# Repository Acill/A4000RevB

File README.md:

# A4000 Replica Project (Based on the Rev B)
Amiga 4000 Replica project. Based on the A4000 Rev B and organized by Paul Rezendes and the generous contributions of the Amiga Community. 

*** IF YOU WISH TO PRODUCE YOUR OWN BOARDS PLEASE USE THE NEW GERBERS LOCATED HERE: https://github.com/Acill/A4000RevB/tree/master/Gerbers-JLCPCB ***

ASCII (PADS) export has been added are are located into the ASCII folder. You can use this to import into other EDA applications. 

By popular request I have added the project into Kicad. its available in the Kicad folder. Please commit any change back here and document them. 

IF YOU PRODUCE BOARDS USING ORIGINAL PROJECT FILES YOU ***MUST*** TELL THE FACTORY TO IMPORT THE GERBERS AS A ***MENTOR PADS FORMAT PROJECT*** The gerbers located here are already good for use as JLCPCB. please read firther information in the gerber section. 

***Thank you Chucky for the locator build hosting! I recomend all go here during your builds for some great help!
A4000 Locator Site: http://locator.reamiga.info/locator.php?project=A4000***

***A4000 Build Guide, Thanks to Chucky! https://wordpress.hertell.nu/?p=1053***

***Shred made a great repo for an updated BOM. Thank you! Please visit the new BOM here: https://a4000-bom.shred.codefloe.page/***

READ THIS: New board files and gerbers have been created and posted to the Github project page. A minor error was discovered that had solder mask covering the ground pads for the support bracket on the mouse and joystick ports. Previous boards work just fine and are not in danger of not working. This is more of a cosmetic update than anything else. Get the new file in the Gerber folder. When using the Chinese sites like JLPCB and PCBway you will need to upload the complete zip gerber archive and email them about the board design. It is done in Mentor PADs. This is a professional layout and it will not usually work with the automatic software they use. I have produced these here in the US and have no problems. Others have used JLPCB with no problems as well. I f you would like a single board and need help I can order sets of 5 and would be happy to sell you one. You can email me through the contact page or directly at info@acill.com and request one. Currently they run $95 shipped in the USA and $110 international.  

# Images

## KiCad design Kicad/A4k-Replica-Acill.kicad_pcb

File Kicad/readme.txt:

Its been a long over due wait, but here is the project in Kicad at last. Please continue to merge here and comment any updates. 

Project and schematics are together in the 7zip archive.

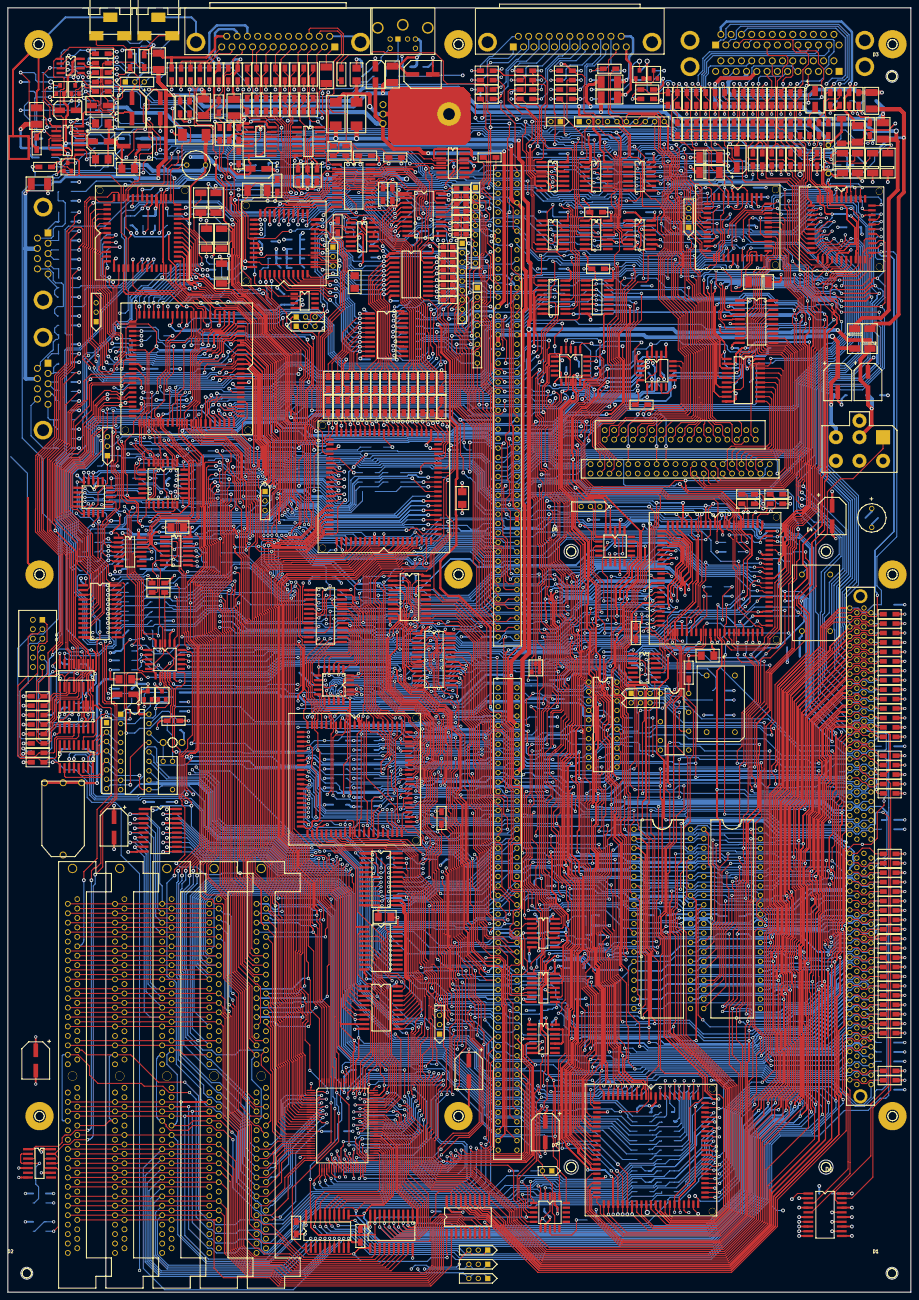
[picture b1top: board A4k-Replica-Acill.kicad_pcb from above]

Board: 4 copper layers, 243.1 x 345.7 mm, 791 parts (0 on the bottom side), 882 nets.

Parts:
BT176: PACKAGE_0000
C102: PACKAGE_0001
C103, C106, C130, C131, C140, C141, C145, C152, C154A, C154B, C193, C195, C201, C211B, C211C, C212, C213, C215, C216, C305, C311, C352, C353, C354, C355, C402A, C406H, C411, C412, C413, C430, C432, C441, C447, C455, C455B, C456, C456B, C457, C457B, C459, C460A, C460B, C460E, C460F, C485, C860, C892: PACKAGE_0002
C104, C177, C178, C179, C205, C211A, C250A, C250C, C300, C350, C400B, C402B, C409, C414, C446, C458B, C460C, C460D, C500, C890, C891, C901, C902, C903, C904, C975, C976, C990: PACKAGE_0003
C150, C406, C708, C711: PACKAGE_0004
C175, C176, C703, C704, C706, C707, C710: PACKAGE_0005
C181, C407: PACKAGE_0006
C185: PACKAGE_0007
C186: PACKAGE_0008
C187, C188, C189, C190, C191, C192, C194, C196, C408: PACKAGE_0009
C198, C318: PACKAGE_0010
C199: PACKAGE_0011
C200, C433, C460G: PACKAGE_0012
C317: PACKAGE_0013
C351, C431: PACKAGE_0014
C400A: PACKAGE_0015
C403, C405, C701: PACKAGE_0016
C404, C443: PACKAGE_0017
C440, C907: PACKAGE_0018
C442, C511, C512, C513, C893, C894: PACKAGE_0019
C450: PACKAGE_0020
C458: PACKAGE_0021
C700, C702, C714: PACKAGE_0022
CN160: PACKAGE_0023
CN175: PACKAGE_0024
CN200, CN302, CN303: PACKAGE_0025
CN300: PACKAGE_0026
CN350: PACKAGE_0027
CN351: PACKAGE_0028
CN352: PACKAGE_0029
CN402, CN403: PACKAGE_0030
CN404: PACKAGE_0031
CN450: PACKAGE_0032
CN452, CN600: PACKAGE_0033
CN651: PACKAGE_0034
CN900: PACKAGE_0035
CN975, CN976: PACKAGE_0036
D1, D2, D3: MTHOLE125-NPT; MTH-125-NPT
D4, D5, D6, D7: MTHOLE150-NPT; MTH-150-NPT
D175: PACKAGE_0037
D176, D360, D361, D362, D363, D500, D501, D502, D503, D504, D505: PACKAGE_0038
D177: PACKAGE_0039
D178: PACKAGE_0040
D300: PACKAGE_0041
D305: PACKAGE_0042
D306, D307: PACKAGE_0043
D507: PACKAGE_0044
EC182, EC184, EC410, EC411: PACKAGE_0003
EC183, EC309, EC362, EC363, EC365, EC366, EC379, EC976, EC977, EC978, EC979, EC980, EC981, EC982, EC983, EC984, EC985, EC986, EC987, EC988, EC989: PACKAGE_0002
EC300, EC301, EC302, EC305, EC306, EC308, EC350, EC351, EC352, EC353, EC354, EC355, EC356, EC357, EC358, EC359, EC360, EC361, EC364: PACKAGE_0019
EC303, EC304, EC451, EC452, EC453, EC454, EC455, EC456, EC457, EC458, EC459, EC460, EC461, EC462, EC463, EC464: PACKAGE_0001
EC307: PACKAGE_0045
EC367, EC371, EC372, EC375, EC376, EC378: PACKAGE_0018
EC368, EC369, EC370, EC373, EC374, EC377: PACKAGE_0014
ER175, ER176: PACKAGE_0003
ER300, ER301, ER302, ER303, ER304, ER305, ER306, ER307, ER363, ER453, ER458, ER459, ER460, ER461: PACKAGE_0001
ER350, ER351, ER352, ER353, ER354, ER355, ER356, ER357, ER358, ER359, ER360, ER361, ER475: PACKAGE_0019
ER362, ER976, ER977, ER978, ER979, ER980, ER981, ER982, ER983, ER984, ER985, ER986, ER987, ER988, ER989: PACKAGE_0002
ER367, ER369, ER370, ER373, ER374, ER377, ER379: PACKAGE_0045
ER368, ER371, ER372, ER375, ER376, ER378: PACKAGE_0021
F175: PACKAGE_0046
FB177, FB308, FB309, FB463, FB476: PACKAGE_0047
FB364, FB401, FB462, FB464: PACKAGE_0048
FB365, FB366, FB975: PACKAGE_0049
FB410, FB411: PACKAGE_0019
FB710: PACKAGE_0001
J100: PACKAGE_0052
J104, J501, J502: PACKAGE_0031
J151: PACKAGE_0053
J212, J214, J852: PACKAGE_0054
J213, J500: PACKAGE_0055
J351, J850: PACKAGE_0056
J352: PACKAGE_0057
J975: PACKAGE_0058
L500: PACKAGE_0011
MT1, MT2, MT3, MT4, MT5, MT6, MT7, MT8, MT9: PACKAGE_0065
Q300, Q901: PACKAGE_0041
Q400: PACKAGE_0039
Q430: PACKAGE_0068
Q440: PACKAGE_0040
R1, R9, R10, R11, R12, R13, R14, R17, R18, R19, R20, R21, R22, R23, R32, R41, R42, R43, R44, R45, R46, R47, R48, R49, R50, R51, R52, R53, R54, R55, R56, R66, R67, R70, R74, R77, R78, R81, R82, R83, R85, R239, R432, R443, R513, R546, R702, R902, R912, R981, R982, R983, R984, R985, R989, R993, R994: PACKAGE_0021
R2, R3, R4, R5, R6, R7, R8, R15, R16, R24, R25, R26, R27, R28, R29, R30, R31, R33, R34, R35, R36, R37, R38, R39, R40, R57, R58, R59, R60, R61, R62, R63, R64, R65, R68, R71, R72, R73, R75, R76, R79, R80, R84, R86, R87, R88, R101, R102, R104, R111, R120, R126, R151, R162, R166, R171, R172, R175, R178, R181, R211, R212, R213, R214, R223, R231, R232, R233, R234, R235, R236, R237, R241, R242, R244, R245, R246, R247, R248, R249, R301, R311, R359, R361, R371, R401, R402, R403, R403B, R403F, R407, R408, R430, R433, R440, R442, R445, R451, R465, R502, R504, R508, R510, R511, R548, R614, R615, R616, R618, R619, R620, R621, R622, R630, R632, R633, R634, R652, R660, R661, R701, R704, R709, R710, R711, R712, R721, R722, R861, R904: PACKAGE_0002
R103, R105, R106, R112, R121, R122, R125, R128, R161, R165, R173, R215, R216, R217, R218, R222, R307, R355, R357, R358, R360, R382, R404, R405, R406, R431, R435, R441, R457, R500, R501, R503, R506, R509, R612, R613, R617, R623, R624, R625, R626, R631, R635, R639, R651, R703, R708, R862, R871, R881, R882, R883, R884, R885, R886, R887, R888, R889, R890, R891, R892, R893, R894, R895, R896, R897, R898, R899, R903, R905, R911: PACKAGE_0003
R127, R206, R302, R356, R456, R458, R458A, R458B, R459, R460, R461, R462, R463, R464, R505, R512, R514, R515: PACKAGE_0019
R167, R168, R169, R170, R306, R381, R403A, R403G, R403H, R434, R507, R545, R720: PACKAGE_0045
R176, R177: PACKAGE_0069
R179: PACKAGE_0070
R180, R182, R240, R243, R305, R403C, R403E, R986, R987, R988, R990, R991, R992: PACKAGE_0014
R207, R208, R520, R521, R522, R523, R524, R525, R526, R527, R528, R529, R530, R531, R532, R533, R534, R535, R536, R537, R538, R539, R540, R541, R542, R543, R547: PACKAGE_0001
R383: PACKAGE_0071
R400: PACKAGE_0072
R403D, R444, R975: PACKAGE_0018
R455A, R455B, R455C, R455D, R455E, R455F, R455G, R455H: PACKAGE_0073
R456A, R456B, R456C, R456D, R456E, R456F, R456G, R456H, R457A, R457B, R457C, R457D, R457E, R457F, R457G: PACKAGE_0074
R457H: PACKAGE_0075
RP176: PACKAGE_0076
RP351: PACKAGE_0077
RP461, RP462, RP463: PACKAGE_0078
U102: PACKAGE_0079
U103: PACKAGE_0080
U104, U154: PACKAGE_0081
U106: PACKAGE_0082
U130: PACKAGE_0083
U131: PACKAGE_0084
U140, U351, U352, U355, U402: PACKAGE_0085
U141: PACKAGE_0086
U145, U455, U456, U458, U704, U707, U708, U891, U903, U904: PACKAGE_0087
U150, U700, U890: PACKAGE_0088
U152: PACKAGE_0089
U175: PACKAGE_0090
U176: PACKAGE_0091
U177, U975, U976: PACKAGE_0092
U178: PACKAGE_0093
U198: PACKAGE_0094
U205, U710: PACKAGE_0095
U211: PACKAGE_0096
U212: PACKAGE_0097
U213: PACKAGE_0098
U215, U311: PACKAGE_0099
U216, U702, U703, U706: PACKAGE_0100
U250: PACKAGE_0101
U261, U850, U851, U852, U853: PACKAGE_0102
U300: PACKAGE_0103
U304, U305, U353: PACKAGE_0104
U350: PACKAGE_0105
U354, U907: PACKAGE_0106
U400: PACKAGE_0107
U403: PACKAGE_0108
U450: PACKAGE_0109
U457: PACKAGE_0110
U459: PACKAGE_0111
U460: PACKAGE_0112
U701: PACKAGE_0113
U711: PACKAGE_0114
U714: PACKAGE_0115
U860: PACKAGE_0116
U892, U893, U894: PACKAGE_0117
U901: PACKAGE_0118
U902: PACKAGE_0119
VC190: PACKAGE_0120
Y176: PACKAGE_0121

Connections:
7M: R223.2, U150.67, U711.13
+5JOY: CN975.7, CN976.7, FB975.2
+5V: C102.2, C103.2, C104.2, C106.2, C130.2, C131.2, C140.2, C141.2, C145.2, C150.2, C152.2, C154A.2, C154B.2, C175.2, C176.2, C177.2, C185.1, C186.2, C187.1, C188.1, C189.1, C190.1, C191.1, C192.1, C205.1, C211A.1, C211B.1, C212.2, C213.2, C215.2, C216.2, C250A.2, C250C.2, C300.1, C305.2, C311.2, C350.1, C351.2, C352.2, C353.2, C354.2, C355.2, C450.1, C455.2, C455B.2, C456.2, C456B.2, C457.2, C457B.2, C458.2, C458B.2, C459.2, C700.1, C701.2, C702.2, C703.2, C704.2, C706.2, C707.2, C708.2, C710.2, C711.2, C714.2, C860.2, C890.2, C891.2, C892.2, C893.2, C894.2, C901.1, C902.1, C903.1, C904.1, C907.1, C975.2, C976.2, CN160.6, CN302.2, CN303.2, CN452.4, CN452.6, CN452.33, CN452.38, CN452.39, CN452.40, CN600.5, CN600.6, CN651.14, CN651.15, CN651.18, CN651.19, CN651.22, CN651.23, CN651.26, CN651.27, CN651.94, CN651.95, CN651.98, CN651.99, CN651.102, CN651.103, CN651.106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
+5V_USER: C511.2, C990.2, F175.2, FB177.1, FB365.2, FB462.2, FB975.1, R383.1
+12V: C193.1, C196.1, CN160.3, CN452.8, CN452.35, CN452.36, CN452.37, CN600.10, D175.1, R178.2, R403.2
+12V_USER: C512.2, D175.2, FB309.1, FB366.2, FB463.2, U304.14
+AUD: C400A.1, C400B.2, R400.2, R401.2, U400.30
+AV: C402A.2, C405.2, C407.1, Q400.2, R403.1, R407.2, U402.4, U403.8
+AVID: C406H.1, C460A.2, C460B.2, C460C.1, C460D.1, C460E.2, C460F.2, C460G.1, C500.1, R465.2, U460.17, U460.34, U460.35, U460.36
+M178: D177.1, D178.1, R178.1
+M179: C200.1, C201.2, D177.3, R179.2, U178.18
+M300: CN300.9, EC309.2, FB309.2
+M350: CN350.14, EC364.2, FB364.1
+M351: FB364.2, R383.2
+M451: CN450.22, EC463.1, FB463.1
+M452: CN450.23, EC462.1, FB462.1
+W177: C199.2, R176.1, R177.1, U198.2, U198.4
+W182: C181.1, CN175.4, EC182.2, FB177.2
+W351: CN352.23, EC366.2, FB366.1
+W352: CN352.12, EC365.2, FB365.1
-5V: C198.2, C513.2, CN452.29, CN600.8, FB464.2, U198.3
-12V: C194.2, C195.1, CN160.2, CN600.20, D176.2, R176.2, R177.2, R404.1
-12V_USER: D176.1, FB308.1, U304.1
-AV: C402B.2, C406.1, C408.2, R404.2, R406.2, U402.11, U403.4
-M301: CN300.10, EC308.2, FB308.2
-M450: CN450.21, EC464.1, FB464.1
ABLUE: CN452.13, D502.1, D503.2, EC458.1, ER458.1, R512.2, U460.33
AGREEN: CN452.9, D501.1, D504.2, EC459.1, ER459.1, J500.3, R511.2, U460.38
AI: C317.2, CN300.18
AO: C318.1, CN300.11
ARED: CN452.5, D500.1, D505.2, EC460.1, ER460.1, R510.2, U460.39
AS: U106.10, U901.12, U907.9
AUDIN: C317.1, R405.1
AUDIO: C402A.1, C402B.1, C403.1, C404.2, C405.1, C406.2, C407.2, C408.1, C409.2, C411.1, C412.1, C413.1, C414.1, C432.1, C442.1, C446.2, C447.2, CN404.2, CN452.74, CN452.76, FB401.2, R402.1, R403D.1, R403H.1, R434.2, R444.2, U400.37
AUDOUT: C443.2, R302.1, R443.1
A_0: CN651.36, R33.1, U150.21, U700.5, U890.19
A_1: CN651.40, R34.1, U150.20, U211.60, U700.4, U890.20, U901.5, U902.6
A_2: CN651.44, R35.1, U175.9, U176.9, U177.11, U211.61, U700.3, U890.21, U907.4
A_3: CN651.48, R36.1, U175.8, U176.8, U177.6, U211.62, U700.48, U890.22, U907.3
A_4: CN651.52, R37.1, U175.7, U176.7, U177.4, U211.63, U704.6, U890.23, U907.6
A_5: CN651.56, R38.1, U175.6, U176.6, U177.3, U211.64, U704.7, U890.24
A_6: CN651.60, R39.1, U175.5, U176.5, U211.65, U704.8, U890.25
A_7: CN651.64, R40.1, U175.4, U176.4, U211.66, U704.9, U890.26
A_8: CN651.33, R41.1, U175.3, U176.3, U211.67, U354.11, U703.4, U890.27
A_9: CN651.37, R42.1, U175.2, U176.2, U211.68, U354.6, U703.5, U890.29
A_10: CN651.41, R43.1, U175.40, U176.40, U211.69, U354.4, U703.6, U890.30
A_11: CN651.45, R44.1, U175.39, U176.39, U211.70, U354.3, U703.7, U890.31
A_12: CN651.49, R45.1, U150.57, U175.38, U176.38, U211.71, U703.8, U890.32, U901.3
A_13: CN651.53, R46.1, U145.18, U150.31, U175.37, U176.37, U211.72, U703.9, U890.33, U901.4, U902.3
A_14: CN651.57, R47.1, U145.16, U150.32, U175.36, U176.36, U211.73, U703.10, U890.34
A_15: CN651.61, R48.1, U145.14, U150.35, U175.35, U176.35, U211.74, U703.11, U890.35
A_16: CN651.65, R49.1, U145.12, U150.19, U175.34, U176.34, U211.75, U702.4, U890.36
A_17: CN651.69, R50.1, U145.9, U150.18, U175.33, U176.33, U211.76, U702.5, U890.37
A_18: CN651.73, R51.1, U145.7, U150.16, U175.32, U176.32, U211.77, U702.6, U890.38
A_19: CN651.77, R52.1, U145.1, U150.15, U175.1, U176.1, U211.59, U702.7, U890.39
A_20: CN651.81, R53.1, U150.14, U211.35, U702.8, U890.40
A_21: CN651.85, R54.1, U140.2, U211.24, U702.9, U890.41
A_22: CN651.89, R55.1, U150.12, U211.53, U702.10, U890.43
A_23: CN651.93, R56.1, U150.11, U702.11, U890.44
A_24: CN651.68, R57.1, U150.10, U706.4, U890.45
A_25: CN651.72, R58.1, U150.9, U706.5, U890.46
A_26: CN651.76, R59.1, U150.7, U706.6, U890.47
A_27: CN651.80, R60.1, U150.6, U706.7, U890.48
A_28: CN651.84, R61.1, U150.5, U706.8, U890.49
A_29: CN651.88, R62.1, U150.4, U706.9, U890.50
A_30: CN651.92, R63.1, U150.3, U706.10, U890.51
A_31: CN651.96, R64.1, U150.2, U706.11, U890.52
BACK0: ER978.2, R983.2, U975.4
BACK1: ER985.2, R987.2, U975.12
BLANK: CN452.26, U455.19, U456.19, U457.19, U459.9
BRIDGE_DIR: U213.15, U250.94
BR_W: U130.6, U211.22, U250.93, U354.13, U891.1, U892.1, U893.1, U894.1
BURST: CN452.16, R508.2
C1: R214.2, U150.65, U212.10, U213.5, U215.1, U400.31, U450.10, U711.4
C3: R215.2, U150.75, U212.9, U213.4, U215.3, U400.32, U711.10
C14O: R501.2, U211.36
C28M: R162.1, U450.25
C28O: CN452.3, R513.2
C28P: R503.2, U458.9, U460.27
CD: CN300.8, EC306.2, ER306.1
CIADR_8: U300.42, U350.42, U354.10
CIADR_9: U300.41, U350.41, U354.7
CIADR_10: U300.39, U350.39, U354.5
CIADR_11: U300.38, U350.38, U354.2
CIARW: U300.24, U350.24, U354.12
CLK90A: R106.1, U860.1, U860.9, U890.63
CLK90B: R111.1, U150.70, U700.58
CLK90_EXP: CN651.126, R112.1
CMA_0: R248.2, U261.12
CMA_1: R240.2, U261.13
CMA_2: R241.2, U261.14
CMA_3: R242.2, U261.15
CMA_4: R243.2, U261.16
CMA_5: R244.2, U261.17
CMA_6: R245.2, U261.18
CMA_7: R246.2, U261.28
CMA_8: R247.2, U261.31
CMA_9: R237.2, U261.32
CPUCLKA: R103.1, U890.10
CPUCLKB: R104.1, U150.43, U152.3, U700.30, U901.7, U902.1, U902.8
CPUCLK_EXP: CN651.135, R105.1
CTS: CN300.5, EC304.1, ER304.1
DIR: U300.13, U353.1
DISABLE: R207.1, U131.10, U205.12, U975.6, U976.6
DKWE: U352.9, U352.10, U400.42
DMAL: U211.18, U400.12
DOE: CN600.93, U700.21
DRA0: U211.43, U212.16, U213.7
DRA10: J214.1, U212.2, U213.11
DRA_1: U211.44, U216.2
DRA_2: U211.45, U216.3
DRA_3: U211.46, U216.4
DRA_4: U211.47, U216.5
DRA_5: U211.48, U216.6
DRA_6: U211.49, U216.7
DRA_7: U211.50, U216.8
DRA_8: U211.51, U216.9
DRA_9: U211.56, U216.10
DRD_0: U250.96, U261.2, U450.8
DRD_1: U250.97, U261.4, U450.7
DRD_2: U250.98, U261.6, U450.6
DRD_3: U250.99, U261.8, U450.5
DRD_4: U250.100, U261.20, U450.4
DRD_5: U250.2, U261.22, U450.3
DRD_6: U250.3, U261.24, U450.2
DRD_7: U250.4, U261.26, U450.84
DRD_8: U250.5, U261.49, U450.82
DRD_9: U250.6, U261.51, U450.81
DRD_10: U250.7, U261.53, U450.80
DRD_11: U250.8, U261.55, U450.79
DRD_12: U250.9, U261.57, U450.78
DRD_13: U250.10, U261.61, U450.77
DRD_14: U250.11, U261.63, U450.76
DRD_15: U250.12, U261.65, U450.75
DRD_16: U211.14, U250.13, U261.3, U400.10, U450.74
DRD_17: U211.13, U250.14, U261.5, U400.9, U450.73
DRD_18: U211.12, U250.15, U261.7, U400.7, U450.72
DRD_19: U211.11, U250.16, U261.9, U400.6, U450.71
DRD_20: U211.10, U250.17, U261.21, U400.5, U450.70
DRD_21: U211.9, U250.19, U261.23, U400.4, U450.69
DRD_22: U211.8, U250.20, U261.25, U400.3, U450.68
DRD_23: U211.7, U250.21, U261.27, U400.2, U450.67
DRD_24: U211.6, U250.22, U261.50, U400.1, U450.66
DRD_25: U211.5, U250.23, U261.52, U400.52, U450.65
DRD_26: U211.4, U250.24, U261.54, U400.51, U450.64
DRD_27: U211.3, U250.25, U261.56, U400.50, U450.63
DRD_28: U211.2, U250.26, U261.58, U400.49, U450.62
DRD_29: U211.1, U250.27, U261.60, U400.48, U450.61
DRD_30: U211.84, U250.29, U261.62, U400.46, U450.60
DRD_31: U211.83, U250.30, U261.64, U400.45, U450.59
DSR: CN300.6, EC305.2, ER305.1
DTR: CN300.20, EC300.2, ER300.1
D_0: CN651.172, R1.1, U176.13, U250.86, U707.9, U891.18
D_1: CN651.176, R2.1, U176.15, U250.85, U707.8, U891.17
D_2: CN651.180, R3.1, U176.17, U250.84, U707.7, U891.16
D_3: CN651.184, R4.1, U176.19, U250.83, U707.6, U891.15
D_4: CN651.188, R5.1, U176.22, U250.82, U707.5, U891.14
D_5: CN651.192, R6.1, U176.24, U250.81, U707.4, U891.13
D_6: CN651.196, R7.1, U176.26, U250.79, U707.3, U891.12
D_7: CN651.200, R8.1, U176.28, U250.78, U707.2, U891.11
D_8: CN651.168, R9.1, U176.14, U250.77, U708.9, U892.11
D_9: CN651.164, R10.1, U176.16, U250.76, U708.8, U892.12
D_10: CN651.160, R11.1, U176.18, U250.75, U708.7, U892.13
D_11: CN651.156, R12.1, U176.20, U250.74, U708.6, U892.14
D_12: CN651.152, R13.1, U176.23, U250.73, U708.5, U892.15
D_13: CN651.148, R14.1, U176.25, U250.72, U708.4, U892.16
D_14: CN651.144, R15.1, U176.27, U250.71, U708.3, U892.17
D_15: CN651.140, R16.1, U176.29, U250.70, U708.2, U892.18
D_16: CN651.169, R17.1, U175.13, U178.11, U250.69, U350.36, U893.18, U903.3
D_17: CN651.173, R18.1, U175.15, U178.12, U250.68, U350.35, U893.17, U903.5
D_18: CN651.177, R19.1, U175.17, U178.13, U250.67, U350.34, U893.16, U903.7
D_19: CN651.181, R20.1, U175.19, U178.14, U250.66, U350.33, U893.15, U903.9
D_20: CN651.185, R21.1, U175.22, U250.65, U350.32, U893.14, U904.3
D_21: CN651.189, R22.1, U175.24, U250.64, U350.31, U893.13, U904.5
D_22: CN651.193, R23.1, U175.26, U250.63, U350.30, U893.12, U904.7
D_23: CN651.197, R24.1, U175.28, U250.62, U350.29, U893.11, U904.9
D_24: CN651.165, R25.1, U175.14, U250.61, U300.36, U890.53, U894.11, U904.8
D_25: CN651.161, R26.1, U175.16, U250.60, U300.35, U890.54, U894.12, U904.6
D_26: CN651.157, R27.1, U175.18, U250.59, U300.34, U890.55, U894.13, U904.4
D_27: CN651.153, R28.1, U175.20, U250.58, U300.33, U890.57, U894.14, U904.2
D_28: CN651.149, R29.1, U175.23, U250.57, U300.32, U890.58, U894.15, U903.8
D_29: CN651.145, R30.1, U175.25, U250.56, U300.31, U890.59, U894.16, U903.6
D_30: CN651.141, R31.1, U175.27, U250.55, U300.30, U890.60, U894.17, U903.4
D_31: CN651.137, R32.1, U150.71, U175.29, U250.54, U300.29, U890.61, U894.18, U902.12, U903.2
E7M: CN600.92, R704.2, U700.31
EA_1: CN600.29, U700.41
EA_2: CN600.27, U700.60
EA_3: CN600.26, U700.61
EA_4: CN600.24, U704.14
EA_5: CN600.21, U704.13
EA_6: CN600.23, U704.12
EA_7: CN600.28, U704.11
EA_8: CN600.30, U703.20, U707.11
EA_9: CN600.32, U703.19, U707.12
EA_10: CN600.34, U703.18, U707.13
EA_11: CN600.36, U703.17, U707.14
EA_12: CN600.38, U703.16, U707.15
EA_13: CN600.39, U703.15, U707.16
EA_14: CN600.41, U703.14, U707.17
EA_15: CN600.43, U703.13, U707.18
EA_16: CN600.45, U702.20, U708.11
EA_17: CN600.47, U702.19, U708.12
EA_18: CN600.52, U702.18, U708.13, U714.15
EA_19: CN600.54, U702.17, U708.14, U714.16
EA_20: CN600.56, U702.16, U708.15, U714.17
EA_21: CN600.58, U702.15, U708.16, U714.18
EA_22: CN600.57, U702.14, U708.17, U714.1
EA_23: CN600.59, U702.13, U708.18, U714.2
ECDAC: CN600.15, R701.2, U700.32
ECLK: CN600.50, U150.64, U300.27, U350.27
ED_0: CN600.75, U250.31
ED_1: CN600.77, U250.32
ED_2: CN600.79, U250.33
ED_3: CN600.81, U250.34
ED_4: CN600.83, U250.35
ED_5: CN600.86, U250.37
ED_6: CN600.84, U250.38
ED_7: CN600.82, U250.39
ED_8: CN600.80, U250.42, U706.20, U714.3
ED_9: CN600.78, U250.43, U706.19, U714.4
ED_10: CN600.76, U250.44, U706.18, U714.5
ED_11: CN600.71, U250.46, U706.17, U714.6
ED_12: CN600.69, U250.47, U706.16, U714.7
ED_13: CN600.67, U250.48, U706.15, U714.8
ED_14: CN600.65, U250.49, U706.14, U714.9
ED_15: CN600.63, U250.50, U706.13, U714.11
EXT90: CN651.13, J100.3
EXTCPU: CN651.112, J104.3
FASTRAMADDR_0: R890.2, U850.12, U851.12, U852.12, U853.12
FASTRAMADDR_1: R889.2, U850.13, U851.13, U852.13, U853.13
FASTRAMADDR_2: R888.2, U850.14, U851.14, U852.14, U853.14
FASTRAMADDR_3: R887.2, U850.15, U851.15, U852.15, U853.15
FASTRAMADDR_4: R886.2, U850.16, U851.16, U852.16, U853.16
FASTRAMADDR_5: R885.2, U850.17, U851.17, U852.17, U853.17
FASTRAMADDR_6: R884.2, U850.18, U851.18, U852.18, U853.18
FASTRAMADDR_7: R883.2, U850.28, U851.28, U852.28, U853.28
FASTRAMADDR_8: R882.2, U850.31, U851.31, U852.31, U853.31
FASTRAMADDR_9: R881.2, U850.32, U851.32, U852.32, U853.32
FC_0: CN651.20, R76.1, U145.5, U150.24, U704.2, U890.16
FC_1: CN651.24, R75.1, U145.3, U150.23, U704.3, U890.17
FC_2: CN651.125, R74.1, U150.22, U704.4, U890.18
FLTLEFT: CN452.1, FB410.1, R443.2, R444.1
FLTRIGHT: CN452.2, FB411.1, R433.2, R434.1
FORW0: ER976.2, R981.2, U975.2
FORW1: ER983.2, R985.2, U975.10
GND: BT176.3, C102.1, C103.1, C104.1, C106.1, C130.1, C131.1, C140.1, C141.1, C145.1, C150.1, C152.1, C154A.1, C154B.1, C175.1, C176.1, C177.1, C178.1, C179.1, C181.2, C185.2, C186.1, C187.2, C188.2, C189.2, C190.2, C191.2, C192.2, C193.2, C194.1, C195.2, C196.2, C198.1, C199.1, C200.2, C201.1, C205.2, C211A.2, C211B.2, C211C.2, C212.1, C213.1, C215.1, C216.1, C250A.1, C250C.1, C300.2, C305.1, C311.1, C350.2, C351.1, C352.1, C353.1, C354.1, C355.1, C400A.2, C400B.1, C406H.2, C450.2, C455.1, C455B.1, C456.1, C456B.1, C457.1, C457B.1, C458.1, C458B.1, C459.1, C460A.1, C460B.1, C460E.1, C460F.1, C460G.2, C485.1, C511.1, C512.1, C513.1, C700.2, C701.1, C702.1, C703.1, C704.1, C706.1, C707.1, C708.1, C710.1, C711.1, C714.1, C860.1, C890.1, C891.1, C892.1, C893.1, C894.1, C901.2, C902.2, C903.2, C904.2, C907.2, C975.1, C976.1, C990.1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
I7M: R222.2, U701.7
IDE_D_0: CN900.4, U903.17
IDE_D_1: CN900.6, U903.15
IDE_D_2: CN900.8, U903.13
IDE_D_3: CN900.10, U903.11
IDE_D_4: CN900.12, U904.17
IDE_D_5: CN900.14, U904.15
IDE_D_6: CN900.16, U904.13
IDE_D_7: CN900.18, U904.11
IDE_D_8: CN900.17, U904.12
IDE_D_9: CN900.15, U904.14
IDE_D_10: CN900.13, U904.16
IDE_D_11: CN900.11, U904.18
IDE_D_12: CN900.9, U903.12
IDE_D_13: CN900.7, U903.14
IDE_D_14: CN900.5, U903.16
IDE_D_15: CN900.3, U903.18
INTCLK: CN452.31, R456.1, U710.4
LATCH_ADR: R165.1, U177.9, U354.9
LEFT0: ER979.2, R982.2, U975.3
LEFT1: ER986.2, R986.2, U975.11
LRBG_0: R527.1, U457.9, U460.18
LRBG_1: R526.1, U457.8, U460.19
LRBG_2: R525.1, U457.7, U460.20
LRBG_3: R524.1, U457.6, U460.21
LRBG_4: R523.1, U457.5, U460.22
LRBG_5: R522.1, U457.4, U460.23
LRBG_6: R521.1, U457.3, U460.24
LRBG_7: R520.1, U457.2, U460.25
LRBG_8: R535.1, U456.9, U460.7
LRBG_9: R534.1, U456.8, U460.8
LRBG_10: R533.1, U456.7, U460.9
LRBG_11: R532.1, U456.6, U460.10
LRBG_12: R531.1, U456.5, U460.11
LRBG_13: R530.1, U456.4, U460.12
LRBG_14: R529.1, U456.3, U460.13
LRBG_15: R528.1, U456.2, U460.14
LRBG_16: R543.1, U455.9, U460.43
LRBG_17: R542.1, U455.8, U460.44
LRBG_18: R541.1, U455.7, U460.1
LRBG_19: R540.1, U455.6, U460.2
LRBG_20: R539.1, U455.5, U460.3
LRBG_21: R538.1, U455.4, U460.4
LRBG_22: R537.1, U455.3, U460.5
LRBG_23: R536.1, U455.2, U460.6
MDAT: U450.20, U975.13
MS_0: CN600.31, U700.81, U704.18
MS_1: CN600.33, U700.54, U704.17
MS_2: CN600.35, U700.45, U704.16
unnamed: CN350.10, EC359.2, ER359.2
unnamed: CN350.1, EC350.2, ER350.2
unnamed: CN350.9, EC358.2, ER358.2
unnamed: CN350.2, EC351.2, ER351.2
unnamed: CN350.8, EC357.2, ER357.2
unnamed: CN350.13, EC362.2, ER362.2
unnamed: CN350.3, EC352.2, ER352.2
unnamed: CN350.7, EC356.2, ER356.2
unnamed: CN350.12, EC361.2, ER361.2
unnamed: CN350.4, EC353.2, ER353.2
unnamed: CN350.6, EC355.2, ER355.2
unnamed: CN350.11, EC360.2, ER360.2
unnamed: CN350.5, EC354.2, ER354.2
unnamed: Q440.3, R445.2
unnamed: Q430.3, R435.2
unnamed: C431.1, R431.2, R432.1
unnamed: C430.1, R405.2, R430.1, U400.33, U402.9
unnamed: C441.1, R441.2, R442.1
unnamed: C432.2, Q430.2, R432.2, U402.5
unnamed: C442.2, Q440.2, R442.2, U402.3
unnamed: C440.1, R440.1, U400.34, U402.13
unnamed: BT176.1, BT176.2, BT176.4, R179.1
unnamed: R170.2, U150.76
unnamed: R168.2, U150.78
unnamed: ER306.2, U305.13
unnamed: ER303.2, U305.1
unnamed: C318.2, R302.2
unnamed: R182.2, U177.1
unnamed: R382.2, U354.1
unnamed: U178.16, VC190.2, Y176.1
unnamed: C178.2, R180.2, U178.17
unnamed: C179.2, R180.1, Y176.2
unnamed: CN352.13, EC370.1, ER370.2
unnamed: CN352.19, EC376.1, ER376.2
unnamed: CN352.18, EC375.1, ER375.2
unnamed: CN352.16, EC373.1, ER373.2
unnamed: CN352.14, EC371.1, ER371.2
unnamed: CN352.15, EC372.1, ER372.2
unnamed: ER367.2, J352.2
unnamed: R307.1, U311.10, U311.12
unnamed: ER307.2, R306.1
unnamed: C443.1, R403C.2, U403.1
unnamed: R897.1, U890.65
unnamed: R888.1, U890.76
unnamed: R886.1, U890.78
unnamed: R898.1, U890.64
unnamed: R889.1, U890.75
unnamed: R896.1, U890.66
unnamed: R887.1, U890.77
unnamed: R899.1, U890.62
unnamed: J104.1, U102.12
unnamed: R101.1, U106.3
unnamed: R101.2, U104.3
unnamed: R103.2, U103.18
unnamed: R104.2, U103.16
unnamed: R509.2, U460.42
unnamed: J500.2, U460.37
unnamed: R524.2, U450.34
unnamed: R455F.2, U455.13
unnamed: CN450.3, ER460.2
unnamed: R542.2, U450.49
unnamed: R501.1, U450.23
unnamed: R534.2, U450.40
unnamed: R526.2, U450.31
unnamed: R508.1, U450.58
unnamed: R457B.2, U457.17
unnamed: R455H.2, U455.11
unnamed: CN450.2, ER461.2
unnamed: R502.1, U450.26
unnamed: R456F.2, U456.13
unnamed: CN450.12, EC451.1, R464.2
unnamed: CN450.1, FB476.2
unnamed: R455E.2, U455.14
unnamed: R505.1, U450.28
unnamed: R503.1, U450.43
unnamed: CN450.15, ER475.1
unnamed: R541.2, U450.50
unnamed: R456H.2, U456.11
unnamed: R533.2, U450.41
unnamed: CN450.11, EC452.1, R463.2
unnamed: R525.2, U450.32
unnamed: R455G.2, U455.12
unnamed: C460C.2, C460D.2, U460.40
unnamed: R456E.2, U456.14
unnamed: R535.2, U450.39
unnamed: CN450.10, ER453.2
unnamed: R527.2, U450.29
unnamed: R457C.2, U457.16
unnamed: R506.1, U450.27
unnamed: R540.2, U450.51
unnamed: CN450.4, ER459.2
unnamed: R500.1, U450.22
unnamed: R456G.2, U456.12
unnamed: R532.2, U450.42
unnamed: R504.2, U450.21
unnamed: R893.1, U860.3, U890.69
unnamed: R892.1, U860.4, U890.71
unnamed: R894.1, U860.2, U890.68
unnamed: R891.1, U860.5, U890.72
unnamed: R890.1, U890.74
unnamed: R883.1, U890.81
unnamed: R885.1, U890.79
unnamed: R882.1, U890.82
unnamed: R884.1, U890.80
unnamed: R881.1, U890.83
unnamed: R102.1, U106.2, U106.6
unnamed: R102.2, U102.1
unnamed: RP176.8, U178.15
unnamed: CN651.121, R660.2
unnamed: CN651.129, R661.2
unnamed: R212.1, U213.18
unnamed: U700.53, U714.19
unnamed: U700.44, U704.19
unnamed: U700.51, U714.13
unnamed: U250.52, U700.36
unnamed: R720.2, U701.11
unnamed: U700.52, U714.12
unnamed: U250.40, U700.34
unnamed: R704.1, U711.11
unnamed: R703.1, U711.8
unnamed: R702.1, U711.6
unnamed: R701.1, U711.3
unnamed: CN351.4, U351.5, U355.10
unnamed: RP351.2, U351.3, U352.3
unnamed: CN351.32, ER370.1, U353.11
unnamed: CN351.6, U351.9, U352.4, U355.13
unnamed: R381.2, U351.1, U351.13
unnamed: CN351.18, ER376.1, U353.3
unnamed: CN351.20, ER375.1, U353.6
unnamed: ER377.1, U355.3
unnamed: RP351.3, U351.11, U352.5, U352.11
unnamed: U700.75, U702.21, U703.21
unnamed: J213.2, U212.13
unnamed: R218.1, U215.6
unnamed: R217.1, U215.2
unnamed: J214.2, U211.55
unnamed: R215.1, U211.39
unnamed: R214.1, U211.40
unnamed: R213.1, U211.37
unnamed: R222.1, R223.1, U211.38
unnamed: J212.2, U211.41
unnamed: R237.1, U212.19
unnamed: R236.1, U212.20
unnamed: R232.1, U212.25
unnamed: R233.1, U212.24
unnamed: R235.1, U212.21
unnamed: R234.1, U212.23
unnamed: R231.1, U212.26
unnamed: U700.35, U707.19, U708.19
unnamed: J351.2, U352.6
unnamed: ER304.2, U305.4
unnamed: CN352.9, EC368.1, ER368.1
unnamed: CN352.17, EC374.1, ER374.2
unnamed: CN352.10, EC378.1, ER378.2
unnamed: CN352.21, EC367.1, ER367.1
unnamed: CN352.22, EC379.1, ER379.2
unnamed: CN352.8, EC377.1, ER377.2
unnamed: CN352.1, EC369.1, ER369.2
unnamed: R460.1, U458.17
unnamed: R459.1, U458.18
unnamed: CN450.9, EC454.1, R462.2
unnamed: CN450.8, EC455.1, R461.2
unnamed: CN450.7, EC456.1, R460.2
unnamed: CN450.6, EC457.1, R459.2
unnamed: U700.43, U706.21
unnamed: U250.51, U700.33, U707.1, U708.1
unnamed: R862.1, U890.73
unnamed: J852.2, U890.12
unnamed: CN175.1, EC184.2, ER175.2
unnamed: CN175.5, EC183.2, ER176.2
unnamed: R311.1, U311.2, U311.4
unnamed: U250.88, U700.37
unnamed: R247.1, U216.16
unnamed: R246.1, U216.17
unnamed: R245.1, U216.18
unnamed: R244.1, U216.19
unnamed: R243.1, U216.20
unnamed: R242.1, U216.21
unnamed: R241.1, U216.22
unnamed: R240.1, U216.23
unnamed: R248.1, U216.15
unnamed: R249.1, U216.14
unnamed: RP176.5, U177.2, U178.7
unnamed: RP176.4, U177.5, U178.6
unnamed: RP176.3, U177.7, U178.5
unnamed: RP176.2, U177.10, U178.4
unnamed: ER302.2, U304.6
unnamed: ER301.2, U304.8
unnamed: ER300.2, U304.11
unnamed: R161.1, U154.3
unnamed: R161.2, U150.68
unnamed: R162.2, U150.80
unnamed: ER305.2, U305.10
unnamed: CN350.16, EC363.2, ER363.1
unnamed: ER363.2, ER378.1, R371.1, U355.6
unnamed: CN450.5, ER458.2
unnamed: CN900.33, U907.2
unnamed: CN900.35, U907.5
unnamed: CN900.36, U907.7
unnamed: R912.1, U907.1
unnamed: R911.1, U902.11
unnamed: U901.13, U902.2, U903.19, U904.19
unnamed: R105.2, U103.14
unnamed: R106.2, U103.9
unnamed: R111.2, U103.7
unnamed: R112.2, U103.5
unnamed: J104.2, U103.2, U103.4, U103.6
unnamed: J100.1, U102.10
unnamed: J100.2, U103.11, U103.13, U103.15
unnamed: D300.3, Q300.1, R305.1, R306.2
unnamed: Q400.1, R407.1, R408.1
unnamed: C409.1, Q400.3, R406.1, R435.1, R445.1
unnamed: R895.1, U860.6, U890.67
unnamed: CN900.31, R902.2
unnamed: Q901.1, R902.1, R903.2
unnamed: U106.8, U140.1
unnamed: U140.3, U150.13
unnamed: R171.1, U106.12
unnamed: R239.1, U216.1
unnamed: CN975.2, EC978.1, ER978.1
unnamed: CN976.3, EC986.1, ER986.1
unnamed: CN975.5, EC982.1, ER982.1
unnamed: CN976.9, EC988.1, ER988.1
unnamed: CN976.4, EC987.1, ER987.1
unnamed: CN975.1, EC976.1, ER976.1
unnamed: CN975.6, EC977.1, ER977.1
unnamed: CN975.9, EC981.1, ER981.1
unnamed: CN976.5, EC989.1, ER989.1
unnamed: CN976.6, EC984.1, ER984.1
unnamed: CN975.4, EC980.1, ER980.1
unnamed: CN975.3, EC979.1, ER979.1
unnamed: R975.1, U976.1
unnamed: U975.1, U976.13
unnamed: CN976.2, EC985.1, ER985.1
unnamed: CN976.1, EC983.1, ER983.1
unnamed: R506.2, U459.10, U460.15
unnamed: J502.2, U460.16
unnamed: ER176.1, U205.8
unnamed: CN200.1, CN200.3, R206.2, U131.11, U205.6
unnamed: R208.1, U141.13, U205.10
unnamed: FB476.1, R457.1, U710.5
unnamed: R458.2, U710.6
unnamed: C500.2, D507.8, U460.41
unnamed: R211.1, U213.12
unnamed: R543.2, U450.48
unnamed: R521.2, U450.37
unnamed: R523.2, U450.35
unnamed: R520.2, U450.38
unnamed: R522.2, U450.36
unnamed: R529.2, U450.46
unnamed: R531.2, U450.44
unnamed: R528.2, U450.47
unnamed: R530.2, U450.45
unnamed: R537.2, U450.55
unnamed: R536.2, U450.57
unnamed: R538.2, U450.54
unnamed: R539.2, U450.52
unnamed: R403E.1, R403F.2, R403G.1, U403.6
unnamed: C441.2, R403B.1, U402.1, U402.2
unnamed: R403D.2, U403.3
unnamed: R403H.2, U403.5
unnamed: C446.1, CN404.3, R403E.2
unnamed: R403A.2, R403B.2, R403C.1, U403.2
unnamed: C431.2, R403F.1, U402.6, U402.7
unnamed: C447.1, CN404.1, R403A.1
unnamed: R457D.2, U457.15
unnamed: R457A.2, U457.18
unnamed: R461.1, U458.16
unnamed: R462.1, U458.15
unnamed: R546.1, U458.19
unnamed: R545.2, U458.1
unnamed: R507.1, U458.14
unnamed: R458B.1, U458.12
unnamed: R513.1, U458.11
unnamed: U152.1, U152.12
unnamed: U152.11, U152.19
unnamed: CN402.1, CN403.2, EC410.1, FB410.2
unnamed: C211C.1, J214.3
unnamed: R216.1, U215.4
unnamed: CN402.2, CN403.1, EC411.1, FB411.2
unnamed: U215.10, U702.23, U703.23, U706.23
unnamed: C433.2, R433.1
unnamed: C433.1, R403G.2, U403.7
unnamed: R125.1, U140.4, U140.10
unnamed: R126.2, U103.1, U103.19
unnamed: R127.1, U106.4
unnamed: R128.1, U106.1
unnamed: R172.1, U106.13
unnamed: R173.2, U150.38
unnamed: R181.2, U178.1
unnamed: R721.2, U711.2, U711.5, U711.9
unnamed: R722.2, U711.12
unnamed: R861.1, U860.11
unnamed: R166.1, U150.39
unnamed: R167.2, U150.79
unnamed: R169.2, U150.77
unnamed: R165.2, U150.72
unnamed: CN303.1, CN303.3, R301.2, R307.2
unnamed: CN302.1, CN302.3, R311.2
unnamed: J501.2, R515.1, U450.11
unnamed: R458A.1, U458.13
unnamed: R456B.2, U456.17
unnamed: R456D.2, U456.15
unnamed: R456A.2, U456.18
unnamed: R456C.2, U456.16
unnamed: R457E.2, U457.14
unnamed: R457F.2, U457.13
unnamed: R457G.2, U457.12
unnamed: R457H.2, U457.11
unnamed: R455A.2, U455.18
unnamed: R455B.2, U455.17
unnamed: R455C.2, U455.16
unnamed: R455D.2, U455.15
unnamed: R547.2, U459.4
unnamed: R451.1, U459.5
unnamed: R548.2, U459.1
unnamed: FB710.1, U700.20
OVL: U150.33, U350.2
PBUSY: CN452.58, D307.1, ER360.1, R357.2, U300.2, U300.43
PIXELSW: CN450.14, CN452.28, R507.2
POT_0X: C411.2, ER982.2, U400.35
POT_0Y: C412.2, ER981.2, U400.36
POT_1X: C413.2, ER989.2, U400.38
POT_1Y: C414.2, ER988.2, U400.39
PPD_0: CN452.63, ER351.1, U350.12
PPD_1: CN452.64, ER352.1, U350.13
PPD_2: CN452.65, ER353.1, U350.14
PPD_3: CN452.66, ER354.1, U350.15
PPD_4: CN452.67, ER355.1, U350.16
PPD_5: CN452.68, ER356.1, U350.17
PPD_6: CN452.69, ER357.1, U350.18
PPD_7: CN452.70, ER358.1, U350.19
PPOUT: CN452.56, D306.1, ER361.1, R358.2, U300.3, U300.44
PSEL: CN452.61, ER362.1, Q300.3, R359.2, U300.4
PSTROBE: CN452.34, D360.1, ER350.1, R355.2, U350.20
RAWLEFT: C440.2, CN452.73, Q440.1, R440.2, R441.1, U402.14
RAWRIGHT: C430.2, CN452.75, Q430.1, R430.2, R431.1, U402.8
RD_0: U850.2, U851.2, U852.2, U853.2, U891.2
RD_1: U850.4, U851.4, U852.4, U853.4, U891.3
RD_2: U850.6, U851.6, U852.6, U853.6, U891.4
RD_3: U850.8, U851.8, U852.8, U853.8, U891.5
RD_4: U850.20, U851.20, U852.20, U853.20, U891.6
RD_5: U850.22, U851.22, U852.22, U853.22, U891.7
RD_6: U850.24, U851.24, U852.24, U853.24, U891.8
RD_7: U850.26, U851.26, U852.26, U853.26, U891.9
RD_8: U850.49, U851.49, U852.49, U853.49, U892.9
RD_9: U850.51, U851.51, U852.51, U853.51, U892.8
RD_10: U850.53, U851.53, U852.53, U853.53, U892.7
RD_11: U850.55, U851.55, U852.55, U853.55, U892.6
RD_12: U850.57, U851.57, U852.57, U853.57, U892.5
RD_13: U850.61, U851.61, U852.61, U853.61, U892.4
RD_14: U850.63, U851.63, U852.63, U853.63, U892.3
RD_15: U850.65, U851.65, U852.65, U853.65, U892.2
RD_16: U850.3, U851.3, U852.3, U853.3, U893.2
RD_17: U850.5, U851.5, U852.5, U853.5, U893.3
RD_18: U850.7, U851.7, U852.7, U853.7, U893.4
RD_19: U850.9, U851.9, U852.9, U853.9, U893.5
RD_20: U850.21, U851.21, U852.21, U853.21, U893.6
RD_21: U850.23, U851.23, U852.23, U853.23, U893.7
RD_22: U850.25, U851.25, U852.25, U853.25, U893.8
RD_23: U850.27, U851.27, U852.27, U853.27, U893.9
RD_24: U850.50, U851.50, U852.50, U853.50, U894.9
RD_25: U850.52, U851.52, U852.52, U853.52, U894.8
RD_26: U850.54, U851.54, U852.54, U853.54, U894.7
RD_27: U850.56, U851.56, U852.56, U853.56, U894.6
RD_28: U850.58, U851.58, U852.58, U853.58, U894.5
RD_29: U850.60, U851.60, U852.60, U853.60, U894.4
RD_30: U850.62, U851.62, U852.62, U853.62, U894.3
RD_31: U850.64, U851.64, U852.64, U853.64, U894.2
READ: CN600.68, U700.38
READLT: U250.92, U701.18
RGA_1: U211.33, U400.29, U450.19
RGA_2: U211.32, U400.28, U450.18
RGA_3: U211.31, U400.27, U450.17
RGA_4: U211.30, U400.26, U450.16
RGA_5: U211.29, U400.25, U450.15
RGA_6: U211.28, U400.24, U450.14
RGA_7: U211.27, U400.23, U450.13
RGA_8: U211.26, U400.22, U450.12
RGB_0: CN452.95, R457H.1, RP461.9
RGB_1: CN452.96, R457G.1, RP461.8
RGB_2: CN452.97, R457F.1, RP461.7
RGB_3: CN452.98, R457E.1, RP461.6
RGB_4: CN452.21, R457D.1, RP461.5, U458.2
RGB_5: CN452.50, R457C.1, RP461.4
RGB_6: CN452.51, R457B.1, RP461.3
RGB_7: CN452.23, R457A.1, RP461.2, U458.3
RGB_8: CN452.91, R456H.1, RP462.9
RGB_9: CN452.92, R456G.1, RP462.8
RGB_10: CN452.93, R456F.1, RP462.7
RGB_11: CN452.94, R456E.1, RP462.6
RGB_12: CN452.46, R456D.1, RP462.5
RGB_13: CN452.47, R456C.1, RP462.4
RGB_14: CN452.48, R456B.1, RP462.3
RGB_15: CN452.25, R456A.1, RP462.2, U458.4
RGB_16: CN452.87, R455H.1, RP463.9
RGB_17: CN452.88, R455G.1, RP463.8
RGB_18: CN452.89, R455F.1, RP463.7
RGB_19: CN452.90, R455E.1, RP463.6
RGB_20: CN452.42, R455D.1, RP463.5
RGB_21: CN452.43, R455C.1, RP463.4
RGB_22: CN452.44, R455B.1, RP463.3
RGB_23: CN452.27, R455A.1, RP463.2, U458.5
RI: CN300.22, EC307.2, ER307.1
RIGHT0: ER980.2, R984.2, U975.5
RIGHT1: ER987.2, R988.2, U975.14
ROMJP0: J151.2, U150.37, U152.5
RTS: CN300.4, EC302.2, ER302.1
RXD: CN300.3, EC303.1, ER303.1
R_W: CN651.5, R81.1, U130.5, U150.26, U215.13, U700.6, U890.11, U902.5
SCLK: R500.2, U211.34, U975.7, U976.7
SIZ0: R78.1, R660.1, U150.27, U700.7, U890.8
SIZ1: R77.1, R661.1, U150.28, U700.8, U890.9
SOG: CN452.53, J502.1, R502.2
SOPT_2: J975.1, R994.2, U976.4
SOPT_3: J975.3, R993.2, U976.5
SOPT_4: J975.5, R992.2, U976.10
SOPT_5: J975.7, R991.2, U976.11
SOPT_6: J975.9, R990.2, U976.12
SOPT_7: J975.11, R989.2, U976.14
TXD: CN300.2, EC301.2, ER301.1
VCDAC: CN452.55, R218.2, U459.3
VREF: C403.2, C404.1, R401.1, R402.2, U402.10, U402.12
XCLK: R458.1, U150.82
ZD: R505.2, U458.6
_68020: J850.2, R871.1, U152.6, U860.12
_AS: CN651.133, R83.1, U150.25, U152.4, U700.9, U860.8, U890.5, U901.1, U902.4
_AVEC: CN651.12, R86.1, R166.2
_BCSYNC: CN452.12, EC453.1, ER453.1, R458A.2
_BCWE: R211.2, U261.47
_BERR: CN651.29, R70.1, U150.40, U700.27
_BG: CN651.105, U700.24, U701.12
_BG30: CN651.159, R71.1, U701.13
_BGACK: CN651.8, R84.1, U700.25
_BHS: R458B.2, U300.21
_BIGZ: U150.83, U700.68
_BINT: CN600.46, R617.1, U700.82
_BLISS: U150.61, U213.17
_BLIT: U150.60, U211.20, U213.8
_BOSS: CN651.17, R711.2, U701.5
_BR: CN651.25, R85.1, U700.23, U701.8
_BRIDGE: U213.14, U250.95
_BUFEN: U860.7, U890.1, U891.19, U892.19, U893.19, U894.19
_C4: C485.2, CN452.17, R451.2
_CACHE: CN600.17, R630.2, U700.47
_CAS_0: R898.2, U850.40, U851.40, U852.40, U853.40
_CAS_1: R897.2, U850.43, U851.43, U852.43, U853.43
_CAS_2: R896.2, U850.41, U851.41, U852.41, U853.41
_CAS_3: R895.2, U850.42, U851.42, U852.42, U853.42
_CBACK: CN651.28, R68.1, U700.50, U890.3
_CBLIT: R212.2, U212.17
_CBR: CN651.147, R712.2, U701.6
_CBREQ: CN651.32, R80.1, U700.49, U890.2
_CCAS_0: R231.2, U261.42
_CCAS_1: R232.2, U261.41
_CCAS_2: R233.2, U261.43
_CCAS_3: R234.2, U261.40
_CCCAS: U211.54, U212.3, U213.3, U216.13, U450.9
_CCRAS: U211.57, U212.27, U213.2
_CCS: CN600.74, U700.2, U700.11, U701.19, U702.22, U703.22, U706.22, U714.14
_CD: U300.9, U305.11
_CDAC: R213.2, U150.66, U212.11, U213.6, U215.5, U711.1
_CHNG: CN351.2, CN352.11, RP351.8, U350.4
_CIA0: U150.47, U350.25
_CIA1: U150.46, U300.25
_CIIN: CN651.132, R87.1, U150.41, U700.18
_CIPL_0: R708.2, U400.13, U701.2
_CIPL_1: R709.2, U400.14, U701.3
_CIPL_2: R710.2, U400.15, U701.4
_CPURST: CN651.109, R121.2, U141.6, U141.9
_CRAS_0: R235.2, U261.34, U261.44
_CRAS_1: R236.2, U261.33, U261.45
_CSYNC: J501.1, J502.3, U211.80, U458.7
_CTS: U300.8, U305.6
_CUTOFF: R408.2, U304.3
_CWE: U211.21, U212.12, U213.1
_DKRD: CN351.30, CN352.2, RP351.9, U400.40
_DKWD: U353.10, U400.41
_DKWDB: CN351.22, ER374.1, U353.8
_DKWEB: CN351.24, ER373.1, U352.8
_DMAEN: CN651.67, R79.1, U890.13
_DS: CN651.97, R82.1, U150.74, U700.10, U901.2
_DSACK0: CN651.91, R65.1, U150.29, U152.17, U860.19, U890.6
_DSACK1: CN651.1, R66.1, U150.30, U152.14, U250.87, U700.12, U860.18, U901.14, U902.19
_DSR: U300.7, U305.8
_DTACK: CN600.66, FB710.2, R639.2
_DTR: U300.11, U304.12, U304.13
_EBCLR: CN600.95, CN651.113, R612.1, U700.63
_EBGACK: CN600.62, R614.1, U700.57
_EBG_0: CN600.64, U700.74
_EBG_1: CN452.83, U700.73
_EBG_2: CN452.82, U700.72
_EBG_3: CN452.81, U700.71
_EBR_0: CN600.60, R618.2, U700.80
_EBR_1: CN452.80, R619.2, U700.79
_EBR_2: CN452.79, R620.2, U700.78
_EBR_3: CN452.78, R621.2, U700.77
_EBR_4: R622.2, U700.76
_EC1: CN600.16, R702.2, U701.1
_EC3: CN600.14, R703.2
_EDS0: CN600.51, U700.62
_EDS1: CN600.98, U700.83
_EDS2: CN600.70, U700.39
_EDS3: CN600.72, U700.40
_EHLT: CN600.55, R615.1, U140.13, U141.2
_EMUL: CN651.31, R73.1
_ERST: CN600.94, R613.1, U140.8
_FAIL: CN160.1, R175.1, U150.56, U178.2, U890.15
_FCS: CN600.97, U215.11, U700.1
_FIR0: ER977.2, U350.10
_FIR1: CN452.59, ER984.2, U211.78, U350.11
_FPUCS: CN651.134, U145.19
_FPURST: CN651.110, U140.11, U141.5
_HLT: CN651.4, R72.1, U700.26
_HSYNC: CN452.20, R463.1, R514.1, U211.81, U458.8
_IDE_CS1: CN900.37, U901.18
_IDE_CS2: CN900.38, U901.17
_IDE_INT: Q901.3, R904.1, U141.11, U902.9
_IDE_IREG: U901.19, U902.7
_IDE_LED: CN900.39, R905.1, U311.1, U311.3
_INDEX: CN351.8, D305.1, ER379.1, RP351.10, U300.26
_INT2: CN600.19, CN651.82, R625.2, U141.10, U350.23, U400.19
_INT3: U211.17, U213.9, U400.20
_INT6: CN600.22, CN651.43, R626.2, U300.23, U400.21
_INTENA: U150.8, U701.9
_IOR: CN900.25, U902.17
_IORST: U140.6, U300.37, U350.37, U351.4, U351.10, U355.4, U400.11, U450.24, U700.29, U975.9, U976.9
_IOW: CN900.23, U902.18
_IPL_0: CN651.120, U701.17
_IPL_1: CN651.124, U701.16
_IPL_2: CN651.128, U701.15
_KBCLK: D363.1, R360.2, U150.44, U205.9, U350.44
_KBDAT: D362.1, ER175.1, R361.2, U141.12, U350.43
_KBLISS: U211.19, U213.16
_KBRST: R120.1, U141.1, U141.3, U150.36
_LED: CN452.71, U304.2, U311.11, U311.13, U350.3
_LLDS: R170.1, U212.4
_LMDS: R169.1, U212.5
_MLD: R504.1, U975.15, U976.15
_MTACK: CN600.48, U700.19
_MTCR: CN600.18, R623.1, U700.46
_MTR: U300.19, U351.2, U351.12, U355.1
_MTRI: CN351.16, U355.8, U355.11
_OECD: U150.54, U250.89, U250.90
_OWN: CN600.7, R624.2, U700.55, U702.3, U703.3, U704.1, U706.3
_PACK: CN452.60, D361.1, ER359.1, R356.2, U350.26
_RAMEN: U106.11, U150.63, U211.25
_RAMSLOT: CN651.16, U150.49
_RAS_0: R894.2, U850.34, U850.44
_RAS_1: R893.2, U850.33, U850.45, U851.34, U851.44
_RAS_2: R892.2, U852.34, U852.44
_RAS_3: R891.2, U852.33, U852.45, U853.34, U853.44
_RDY: CN351.34, ER369.1, J351.1, RP351.5, U350.9
_REGEN: U150.62, U211.23
_RESET: CN600.53, CN651.117, CN900.1, R122.2, R616.1, U140.5, U140.9, U140.12, U141.4, U141.8, U211.16
_RMC: CN651.108, R88.1, U700.15
_ROMEN: U150.53, U152.2, U175.12, U176.12
_RTCR: RP176.7, U150.52, U178.8
_RTCW: RP176.6, U150.50, U178.10
_RTS: U300.10, U304.4, U304.5
_RXD: U305.3, U400.44
_R_W: U215.12, U850.11, U851.11, U852.11, U853.11, U903.1, U904.1
_SBR: CN651.9, R652.1, U700.16
_SCSI: CN651.66, U150.45, U901.6
_SEL0: CN351.10, J352.3, U300.15, U352.1, U352.2
_SEL1: CN351.12, U300.16, U352.12, U352.13
_SEL2: J352.1, U300.17
_SEL3: ER368.2, U300.18
_SIDE: U300.14, U353.13
_SLAVE_0: CN600.9, R631.2, U700.67
_SLAVE_1: CN452.86, R632.2, U700.66
_SLAVE_2: CN452.85, R633.2, U700.65
_SLAVE_3: CN452.84, R634.2, U700.64
_SLAVE_4: R635.2, U700.59
_STEP: U300.12, U353.4
_STERM: CN651.21, R67.1, U150.73, U700.13, U890.4
_TRK0: CN351.26, ER372.1, RP351.6, U350.8
_TXD: U304.9, U304.10, U400.43
_UMDS: R168.1, U212.6
_UUDS: R167.1, U212.7
_VC1: CN452.32, ER475.2, R217.2
_VC3: CN452.57, R216.2, U459.2
_VSYNC: CN452.24, CN452.54, R464.1, U205.11, U211.79, U350.21
_WAIT: CN651.55, R651.1, U700.22, U890.7
_WE0: R899.2, U850.47, U851.47, U852.47, U853.47
_WPROT: CN351.28, ER371.1, RP351.7, U350.7
_XCLKEN: CN452.14, EC461.1, ER461.1, R151.2, U150.81

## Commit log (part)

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2018-04-23 BOM OCR and corrections by tbtorro (Jozsef Vamosi) based on A4000 Service Addendum
2018-04-23 Schematics (OLD) V1.37
    Original schematics prior to remake from reverse engineering and replica project. Used here for historical and comparisons.
2018-06-21 Add files via upload
    This is for review before telling the company doing the work on the layout to move forward! Please use the free PADS viewer and report anything you see that doesnt belong or is wrong. The company und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
2018-06-21 Add files via upload
    PDF version of RC1 for final review.
2020-01-13 Added completed build images
    I've added the completed build images as requested in high resolution. Hopefully, this helps out those looking for it.
2021-03-16 Fix a few errors in BOM
2021-05-28 Delete A4000B_BOM.xls
    Out of date, and no longer valid.
2021-05-28 Add files via upload
    Updated BOM. Thanks to Grim82!
2024-05-15 New Gerbers with the updated silkscreens and pick and place files
2024-05-15 Add pictures
2024-05-21 Add files via upload
    Alternative BOM but with no links to them for purchase. Several users wanted a cleaner BOM. Some changes made but nothing that will change builds over previous.
2024-05-30 Added missing labels for U702 and U711
2025-02-08 Update link to BOM project
2025-03-21 Update README.md
    Clarified making your own gerbers from project files
2026-04-18 Add files via upload
    Initial Kicad release project files. Created in the latest release of Kicad and tested as of April 2026.
2026-04-27 Add files via upload
    ASCII export from PADs. Tested good for import into Kicad and others. It is recommended you follow your preferred applications import guides for linking to board project file.
2026-04-27 Revise readme with ASCII export details
    Updated readme to reflect completion of ASCII export for schematics.
2026-04-27 Add files via upload
    Project and schematics
2026-04-27 Revise readme to clarify project archive contents
    Updated the readme to reflect project and schematics packaging.
